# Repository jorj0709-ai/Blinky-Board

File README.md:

# Blinky-Board
A custom blinky board PCB using a CD4017 counter to light 10 LEDs in sequence with adjustable speed.
I made this project to learn PCB design and try and understand a little bit more about hardware development.

BOM:
Timer IC             --> NEE555P
IC to Control LEDs   --> CD4017
Various values       --> Resistors
Various values       --> Capacitors
10x                  --> LEDs

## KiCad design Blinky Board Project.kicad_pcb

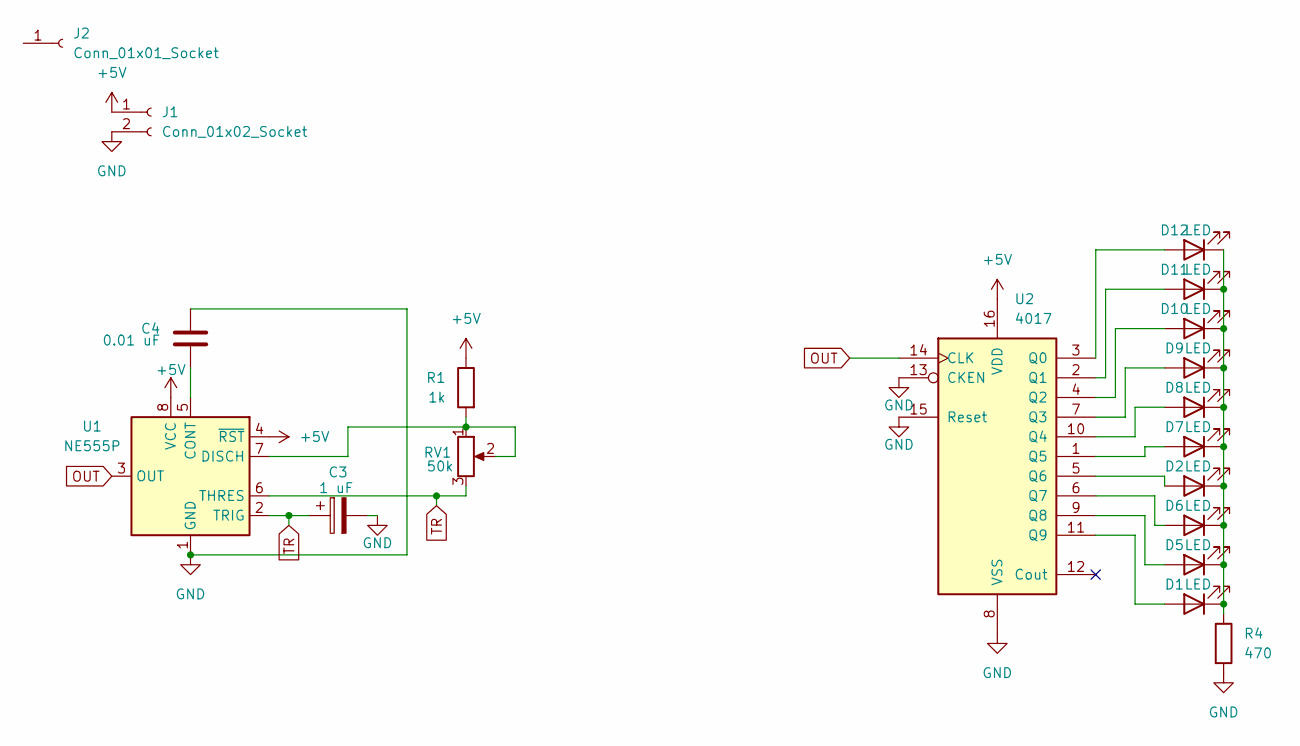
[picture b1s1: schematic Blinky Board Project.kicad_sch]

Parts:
C3: 1 uF; CP_Radial_D5.0mm_P2.00mm
C4: 0.01 uF; C_Disc_D7.5mm_W2.5mm_P5.00mm
D1, D2, D5, D6, D7, D8, D9, D10, D11, D12: LED; LED_D3.0mm
J1: Conn_01x02_Socket; PinHeader_1x02_P2.54mm_Vertical
J2: Conn_01x01_Socket; PinHeader_1x01_P2.54mm_Vertical
R1: 1k; R_Axial_DIN0207_L6.3mm_D2.5mm_P7.62mm_Horizontal
R4: 470; R_Axial_DIN0207_L6.3mm_D2.5mm_P7.62mm_Horizontal
RV1: 50k; Potentiometer_Vishay_T93YA_Vertical
U1: NE555P; DIP-8_W7.62mm
U2: 4017; N16

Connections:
+5V: J1.1, R1.1, U1.4 (~RST), U1.8 (VCC), U2.16 (VDD)
GND: C3.2, C4.2, J1.2, R4.2, U1.1 (GND), U2.8 (VSS), U2.13 (CKEN), U2.15 (Reset)
unnamed: D1.2 (A), U2.11 (Q9)
unnamed: D1.1 (K), D2.1 (K), D5.1 (K), D6.1 (K), D7.1 (K), D8.1 (K), D9.1 (K), D10.1 (K), D11.1 (K), D12.1 (K), R4.1
unnamed: D2.2 (A), U2.5 (Q6)
unnamed: D5.2 (A), U2.9 (Q8)
unnamed: D6.2 (A), U2.6 (Q7)
unnamed: D7.2 (A), U2.1 (Q5)
unnamed: D8.2 (A), U2.10 (Q4)
unnamed: D9.2 (A), U2.7 (Q3)
unnamed: D10.2 (A), U2.4 (Q2)
unnamed: D11.2 (A), U2.2 (Q1)
unnamed: D12.2 (A), U2.3 (Q0)
unnamed: C4.1, U1.5 (CONT)
unnamed: R1.2, RV1.1, RV1.2, U1.7 (DISCH)
OUT: U1.3 (OUT), U2.14 (CLK)
TR: C3.1, RV1.3, U1.2 (TRIG), U1.6 (THRES)

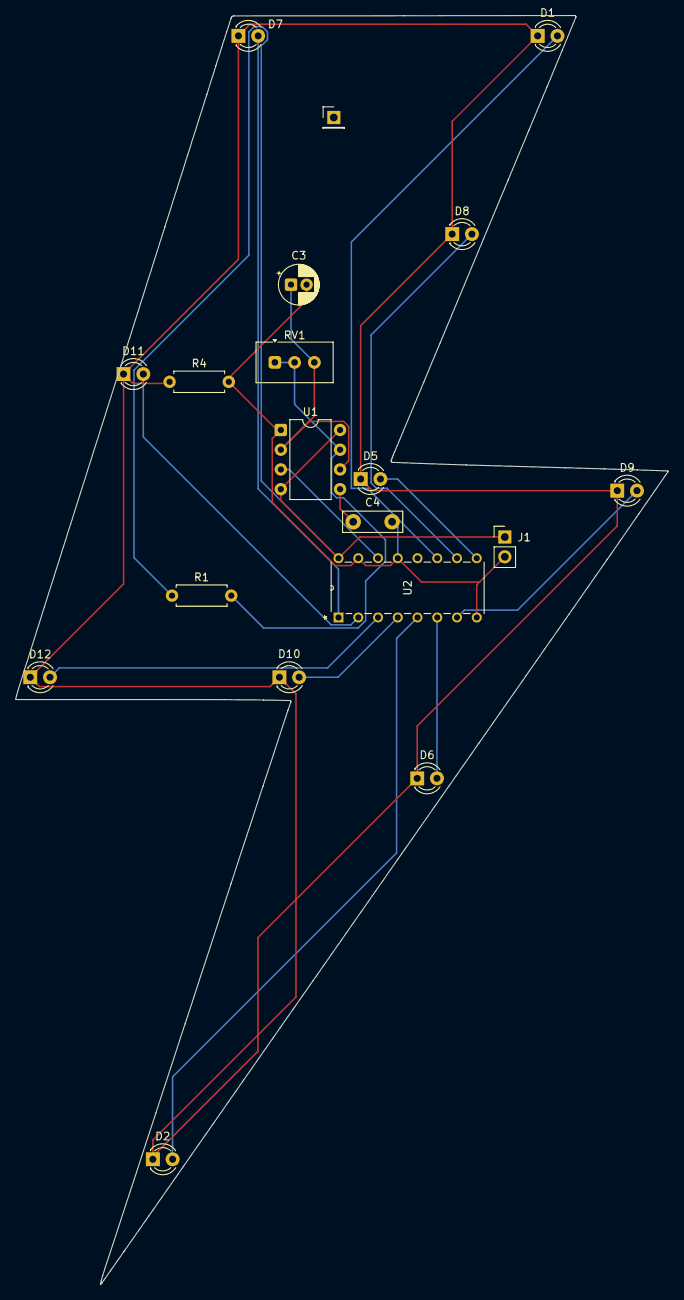
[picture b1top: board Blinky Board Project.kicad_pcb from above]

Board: 2 copper layers, 83.9 x 163.2 mm, 19 parts (0 on the bottom side), 17 nets.

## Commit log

2026-04-16 Revise README with project details and images
    Updated project description and added images and BOM details.
2026-04-16 Revise README description for clarity
    Updated project description for clarity and focus on hardware development.
